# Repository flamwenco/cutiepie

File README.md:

# cutiepie
A funky little 10.5u with dual 1.75u spacebars. Support for 3u and 4u spacebar bottom row layouts has been added, as well as support for 2x2u's using the 4u top. 2u's are forced stabless, otherwise a redesign of the pcb layout would have been necessitated.

## Layout options

[An ortho pcb](https://github.com/flamwenco/cutiepie/tree/mistress/KiCad%20Project%20Files/ortho%20pcb) is also now available as well.

The vial firmware has been updated to visually support uniform stagger, regular stagger, and ortho, but your existing firmware will also work since the pinouts have not changed.

## Production files
The current version of this pcb that supports all above layouts has been ordered and confirmed to work, but I am not responsible for your orders with a pcb manu. No support will be provided, order at your own risk.

You will also need a daughterboard for this keyboard. It was designed around the ai03 C3 daughterboard.

## Case files
Case files are provided in this repo for 3d printing.

The case is designed around m2 screws and heatset inserts. The top will need 6 M2x4mm inserts, and M2x5mm screws. The daughterboard mounting in the bottom will need 4 M2x3mm inserts, and M2x4mm screws.

The cutouts for the feet in the bottom of the case are sized for primekb feet.

## Special Thanks
- [SST60](https://github.com/dededecline/SST60), this project heavily lifts the rp2040 wiring from it, without it I wouldn't have even known where to start
- 4u spacebar footprint is by [drhigsby](https://github.com/drhigsby)
- Thick plates were created from plates generated by bears' [Keyboard Case Generator](https://github.com/gleorepo/Keyboard-Case-Generator)
- Symmetric case and plate were modified by Chronomap
- [Baconspoon](https://github.com/baconspoon85/) for going above and beyond with new hotswap pcbs, layouts, case mods, and all sorts of other stuff.

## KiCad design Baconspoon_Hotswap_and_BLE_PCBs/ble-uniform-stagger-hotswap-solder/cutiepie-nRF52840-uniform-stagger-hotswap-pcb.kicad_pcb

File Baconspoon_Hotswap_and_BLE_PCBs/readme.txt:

Included in this directory are several PCB and plate files for Cutiepie by Flamwenco. Pay close attention to compatibility notes. Most of these PCB's and plates are NOT compatible with the original 2x1.75u and 3u case tops, or the original non-symmetrical case bottom. Choose a plate option that will support your desired layout, including stabilizers.

UPDATE: Added models for thick plates at /Baconspoon_Hotswap_and_BLE_PCBs/thick-plate-models. There are separate models for standard row stagger, uniform row stagger, and ortho. All three plates are for the 2x2u or 4u spacebar layout only. Stagger plates support the ISO P-key.

UPDATE: Added model for ortho PCB top case at /Case Files/Symmetrical 4u 2x2u Case/Orthopie Top Case - Baconspoon
This model is only compatible with the symmetrical case (2x2u or 4u spacebar) and add a central half unit blocker where the two alpha sections split.
	
-Hotswap, Uniform Stagger PCB
	-Integrated RP2040
	-No ISO Enter support
	-Uses uniform 0.25u stagger, as with the original cutiepie
	-Support for both 2u x 2 and 4u stabilizers.
	-Requires the symmetrical uniform or dual stagger plate for 2u stabilizer support.
	-Requires the symmetrical top and bottom cases with only 2x2u or 4u spacebar support.
	-Compatible with original "cutiepie2040" PCB firmware due to 1-for-1 pinout match.

-Hotswap, Standard Stagger PCB
	-Integrated RP2040
	-No ISO Enter support
	-Option for uniform 0.25u stagger, or traditional 0.5u stagger between the "A" and "Z" row.
	-Support for both 2u x 2 and 4u stabilizers.
	-Requires the symmetrical standard or dual stagger plate for 2u stabilizer support.
	-Requires the symmetrical top and bottom cases with only 2x2u or 4u spacebar support.
	-Compatible with original "cutiepie2040" PCB firmware due to 1-for-1 pinout match.

-Hotswap, Dual Stagger PCB
	-Made to replace uniform and standard stagger hotswap PCBs by supporting both layouts
	-Restores ISO P key support. To access stab support for ISO P, it is necessary to remove the hotswap socket for 1.5u P. Alternatively, a custom plate can be cut to support  a plate mount stabilizer. DXF and Gerber files for that plate will be made available in the repo.
	-Other features and case requirements are identical to the PCBs being replaced.

-Hotswap and Solder, Ortho PCB
	-Integrated RP2040
	-Supports 2x2u, 4u, and 2x1.75u spacebar layouts from original Flamwenco orthopie design.
	-2x1.75u spacebar layout is solder only and requires the removal of a breakaway tab to fit the appropriate case.
	-3u spacebar layout is not supported.
	-All supported layouts can be soldered. Soldered switches will be north-facing. Hotswap sockets are south-facing.
	-Compatible with vial firmware release for "orthopie" PCB due to 1-for-1 pinout match.

-Solder Only, Dual Stagger (Uniform and Standard) BLE PCB
	-Still in development
	-Integrated nRF52840 via Holyiot-18010-nRF52840 module
	-No ISO Enter support
	-Option for traditional 0.5u stagger between the "A" and "Z" row.
	-Support for both 2u x 2 and 4u stabilizers.
	-Requires the symmetrical standard or dual stagger plate for 2u stabilizer support.
	-Requires the symmetrical top and bottom cases with only 2x2u or 4u spacebar support.
	-Custom ZMK firmware

-Dual Stagger Plate
	-Maintains ISO switch and stabilizers support.
	-"Z" row switch cutouts support both standard and uniform stagger.
	-May be difficult to achieve perfect left-to-right alignment with 3-pin switches. 5-pin is recommended.
	-Gerbers for FR4 plates included with KiCad project files.

-Standard Stagger and Uniform Stagger Plates (separate)
	-Maintains ISO switch and stabilizers support for future compatibility with symmetrical case PCBs supporting ISO Enter.
	-Separate plates for each stagger option for better alignment with 3-pin switches.
	-Gerbers for FR4 plates included with KiCad project files.

-Ortho Plus Dual Stagger Universal Plate
	-Supports both ortho and stagger layout options.
	-Supports only 2x2u and 4u spacebar layouts.
	-Supports ISO P key with stabilizers.
	-Requires summetrical case design for 2x2u and 4u spacebar layouts.
	-Ortho build requires case with central 1.5u blocker to cover holes for staggered layouts.

-Ortho Plate
	-Supports ortho only, either 4u, 2x2u, or 2x1.75u spacebar layouts.
	-Works with or without central 1.5u blocker in the case.

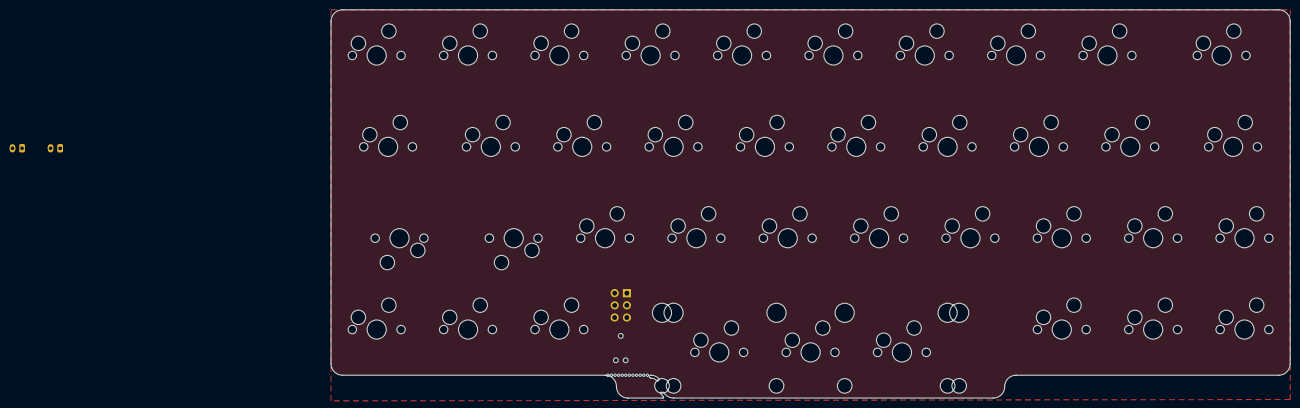
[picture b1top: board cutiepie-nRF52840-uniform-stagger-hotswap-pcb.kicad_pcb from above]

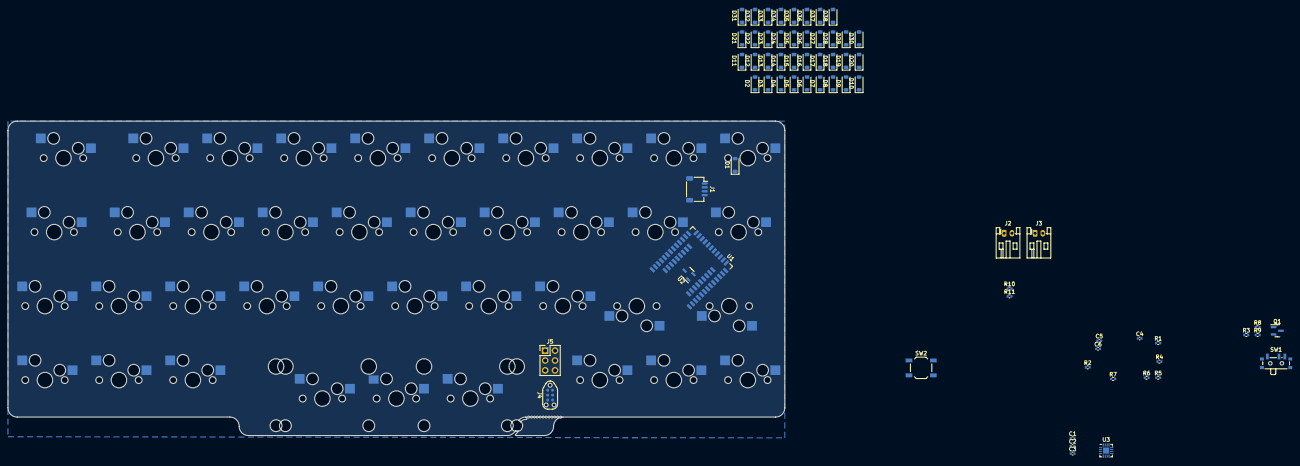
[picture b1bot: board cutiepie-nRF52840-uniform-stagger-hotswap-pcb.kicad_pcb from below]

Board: 2 copper layers, 200.0 x 81.0 mm, 106 parts (67 on the bottom side), 73 nets, no tracks yet.

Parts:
C1, C2: 1uF; C_0402_1005Metric
C3: 100nF; C_0402_1005Metric
C4, C5, C6: 4u7; C_0402_1005Metric
D1, D2, D3, D4, D5, D6, D7, D8, D9, D10, D11, D12, D13, D14, D15, D16, D17, D18, D19, D20, D21, D22, D23, D24, D25, D26, D27, D28, D29, D30, D31, D32, D33, D34, D35, D36, D37, D38: 1N4148W; D_SOD-123
H1: Cutiepie Tab; cutiepie-tab
J1: SM04B; JST_SH_SM04B-SRSS-TB_1x04-1MP_P1.00mm_Horizontal
J2, J3: Battery; JST_PH_S2B-PH-K_1x02_P2.00mm_Horizontal
J4: TC2030_SWD; CON_TC2030_outlined
J5: Conn_02x03_Counter_Clockwise; PinHeader_2x03_P2.54mm_Vertical
MX1, MX2, MX3, MX4, MX5, MX6, MX7, MX8, MX9, MX12, MX13, MX14, MX15, MX16, MX17, MX18, MX19, MX22, MX23, MX24, MX25, MX26, MX27, MX28, MX29, MX30, MX31, MX32, MX33, MX37, MX38, MX39: CPG151101S11; MXOnly-1U-Hotswap
MX10, MX21: CPG151101S11; MXOnly-1.5U-Hotswap
MX11, MX20: CPG151101S11; MXOnly-1.25U-Hotswap
MX34, MX35, MX36: CPG151101S11; MXOnly-2U-Hotswap-ReversedStabilizers
Q1: 2N7002; SOT-23
R1: 47k; R_0402_1005Metric
R2, R9: 10k; R_0402_1005Metric
R3: 100k; R_0402_1005Metric
R4, R5, R6, R7: 1k5; R_0402_1005Metric
R8: 100; R_0402_1005Metric
R10: 806kΩ; R_0402_1005Metric
R11: 2MΩ; R_0402_1005Metric
SW1: SW_SPDT; SW_SPDT_PCM12
SW2: RESET; SW_SPST_TL3342
U1: nRF52840_holyiot_18010
U2: XC6206P332MR; SOT-23-3
U3: BQ24075RGT; VQFN-16-1EP_3x3mm_P0.5mm_EP1.6x1.6mm

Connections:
+3V3: C2.2, C3.2, J4.1 (VCC), J5.1, U1.14 (VDD_nRF), U2.2 (VO)
+5V: C4.1, J1.1, R8.1, U1.22 (VBUS), U3.13 (IN)
+BATT: C6.1, J2.1, J3.1, R3.1, U3.2 (BAT), U3.3 (BAT)
+VSW: C1.2, C5.1, R7.2, R10.1, U2.3 (VI), U3.6 (EN1), U3.10 (OUT), U3.11 (OUT)
GND: C1.1, C2.1, C3.1, C4.2, C5.2, C6.2, J1.4, J2.2, J3.2, J4.5 (GND), J5.5, Q1.2 (S), R1.1, R2.2, R4.1, R5.1, R9.2, R11.2, SW1.3 (C), SW2.2, U1.1 (GND), U1.25 (GND), U1.37 (GND), U2.1 (GND), U3.4 (~CE), U3.5 (EN2), U3.8 (VSS), U3.17 (VSS)
unnamed: D1.2 (A), MX1.2 (ROW)
unnamed: D2.2 (A), MX2.2 (ROW)
unnamed: D3.2 (A), MX3.2 (ROW)
unnamed: D4.2 (A), MX4.2 (ROW)
unnamed: D5.2 (A), MX5.2 (ROW)
unnamed: D6.2 (A), MX6.2 (ROW)
unnamed: D7.2 (A), MX7.2 (ROW)
unnamed: D8.2 (A), MX8.2 (ROW)
unnamed: D9.2 (A), MX9.2 (ROW)
unnamed: D10.2 (A), MX10.2 (ROW)
unnamed: D11.2 (A), MX11.2 (ROW)
unnamed: D12.2 (A), MX12.2 (ROW)
unnamed: D13.2 (A), MX13.2 (ROW)
unnamed: D14.2 (A), MX14.2 (ROW)
unnamed: D15.2 (A), MX15.2 (ROW)
unnamed: D16.2 (A), MX16.2 (ROW)
unnamed: D17.2 (A), MX17.2 (ROW)
unnamed: D18.2 (A), MX18.2 (ROW)
unnamed: D19.2 (A), MX19.2 (ROW)
unnamed: D20.2 (A), MX20.2 (ROW)
unnamed: D21.2 (A), MX21.2 (ROW)
unnamed: D22.2 (A), MX22.2 (ROW)
unnamed: D23.2 (A), MX23.2 (ROW)
unnamed: D24.2 (A), MX24.2 (ROW)
unnamed: D25.2 (A), MX25.2 (ROW)
unnamed: D26.2 (A), MX26.2 (ROW)
unnamed: D27.2 (A), MX27.2 (ROW)
unnamed: D28.2 (A), MX28.2 (ROW)
unnamed: D29.2 (A), MX29.2 (ROW)
unnamed: D30.2 (A), MX30.2 (ROW)
unnamed: D31.2 (A), MX31.2 (ROW)
unnamed: D32.2 (A), MX32.2 (ROW)
unnamed: D33.2 (A), MX33.2 (ROW)
unnamed: D34.2 (A), MX34.2 (ROW), MX35.2 (ROW)
unnamed: D35.2 (A), MX36.2 (ROW)
unnamed: D36.2 (A), MX37.2 (ROW)
unnamed: D37.2 (A), MX38.2 (ROW)
unnamed: D38.2 (A), MX39.2 (ROW)
unnamed: Q1.1 (G), R8.2, R9.1
unnamed: R5.2, R6.1
unnamed: R3.2, SW1.1 (A)
unnamed: R4.2, U3.12 (ILIM)
unnamed: R6.2, U3.16 (ISET)
unnamed: R1.2, U3.14 (TMR)
unnamed: R2.1, U3.1 (TS)
unnamed: R7.1, U3.9 (~CHG)
RESET: J4.3 (~RST), J5.3, SW2.1, U1.21 (P0.18-RESET)
SWDCLK: J4.4 (SWCLK), J5.4, U1.31 (SWDCLK)
SWDIO: J4.2 (SWDIO), J5.2, U1.32 (SWDIO)
SWO: J4.6 (SWO), J5.6
SYSOFF: Q1.3 (D), SW1.2 (B), U3.15 (SYSOFF)
USB_D+: J1.3, U1.24 (D+)
USB_D-: J1.2, U1.23 (D-)
VSENSE: R10.2, R11.1, U1.11 (P0.31-LF-A)
col0: MX1.1 (COL), MX11.1 (COL), MX21.1 (COL), MX31.1 (COL)
col1: MX2.1 (COL), MX12.1 (COL), MX22.1 (COL), MX32.1 (COL)
col2: MX3.1 (COL), MX13.1 (COL), MX23.1 (COL), MX33.1 (COL)
col3: MX4.1 (COL), MX14.1 (COL), MX24.1 (COL)
col4: MX5.1 (COL), MX15.1 (COL), MX25.1 (COL), MX34.1 (COL), MX35.1 (COL)
col5: MX6.1 (COL), MX16.1 (COL), MX26.1 (COL), MX36.1 (COL)
col6: MX7.1 (COL), MX17.1 (COL), MX27.1 (COL)
col7: MX8.1 (COL), MX18.1 (COL), MX28.1 (COL), MX37.1 (COL)
col8: MX9.1 (COL), MX19.1 (COL), MX29.1 (COL), MX38.1 (COL)
col9: MX10.1 (COL), MX20.1 (COL), MX30.1 (COL), MX39.1 (COL)
row0: D1.1 (K), D2.1 (K), D3.1 (K), D4.1 (K), D5.1 (K), D6.1 (K), D7.1 (K), D8.1 (K), D9.1 (K), D10.1 (K)
row1: D11.1 (K), D12.1 (K), D13.1 (K), D14.1 (K), D15.1 (K), D16.1 (K), D17.1 (K), D18.1 (K), D19.1 (K), D20.1 (K)
row2: D21.1 (K), D22.1 (K), D23.1 (K), D24.1 (K), D25.1 (K), D26.1 (K), D27.1 (K), D28.1 (K), D29.1 (K), D30.1 (K)
row3: D31.1 (K), D32.1 (K), D33.1 (K), D34.1 (K), D35.1 (K), D36.1 (K), D37.1 (K), D38.1 (K)

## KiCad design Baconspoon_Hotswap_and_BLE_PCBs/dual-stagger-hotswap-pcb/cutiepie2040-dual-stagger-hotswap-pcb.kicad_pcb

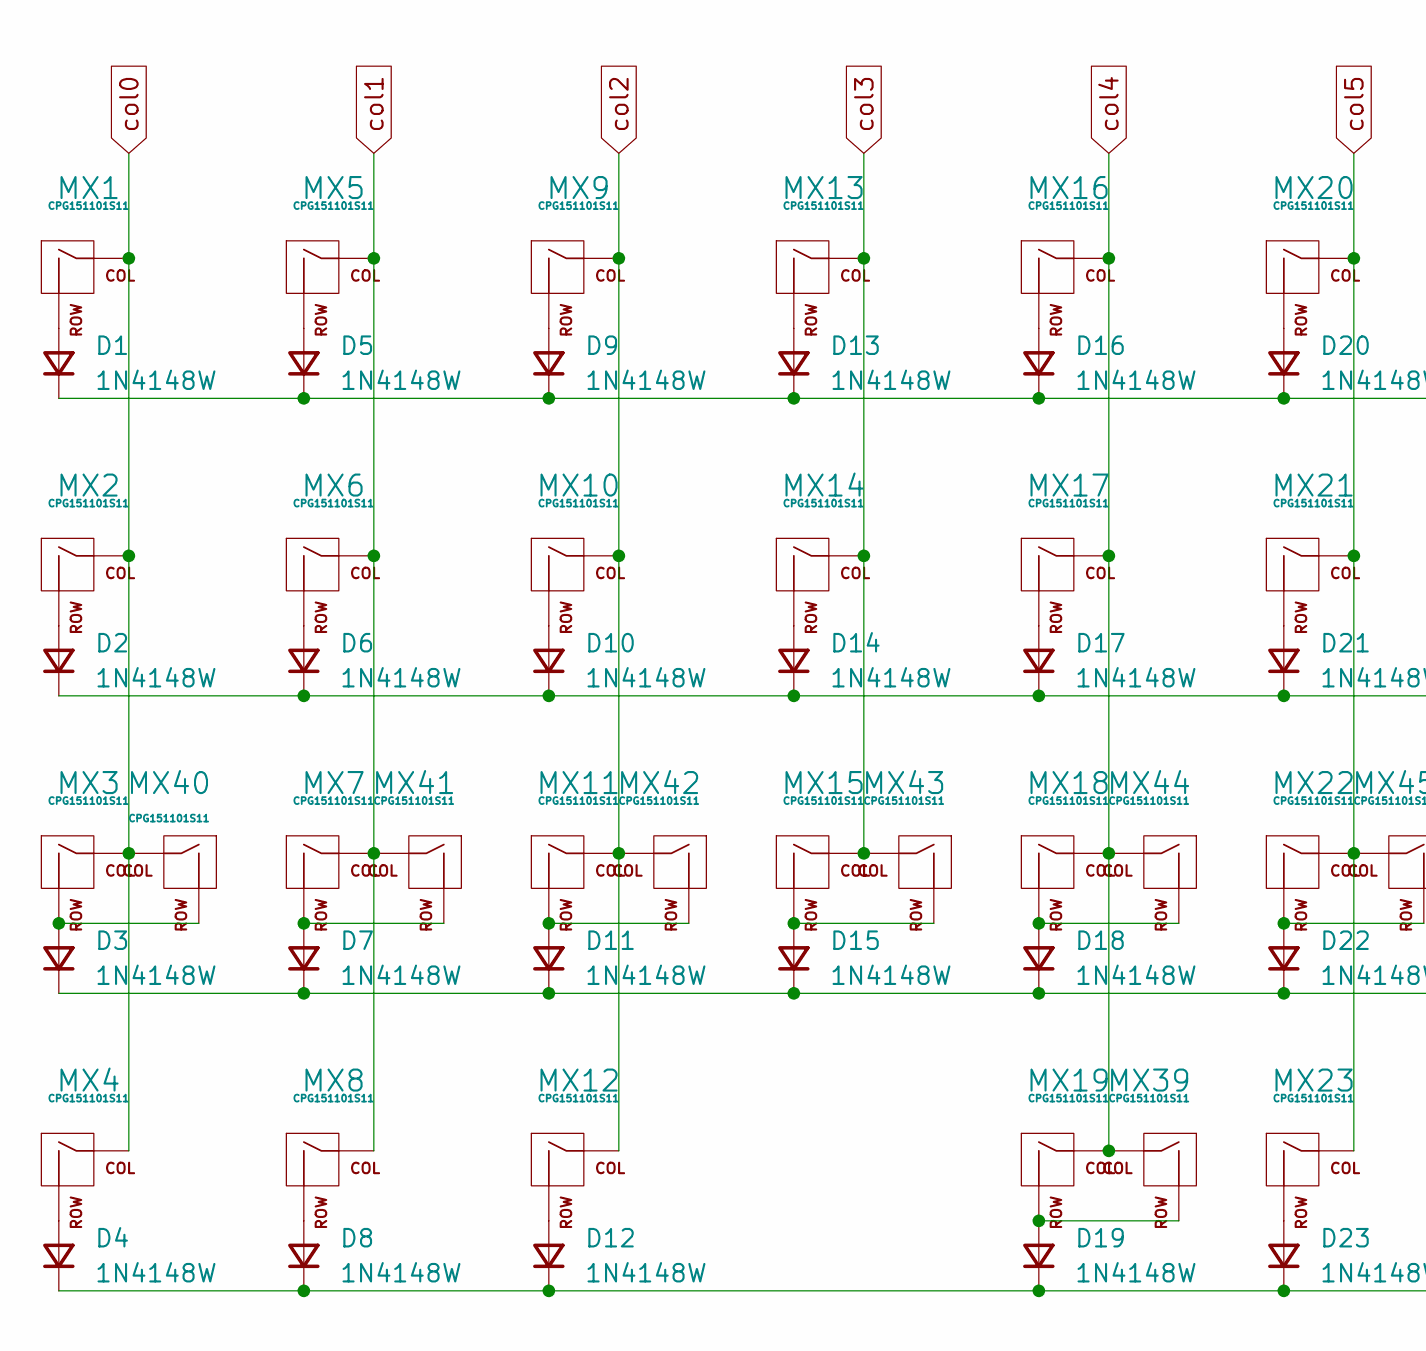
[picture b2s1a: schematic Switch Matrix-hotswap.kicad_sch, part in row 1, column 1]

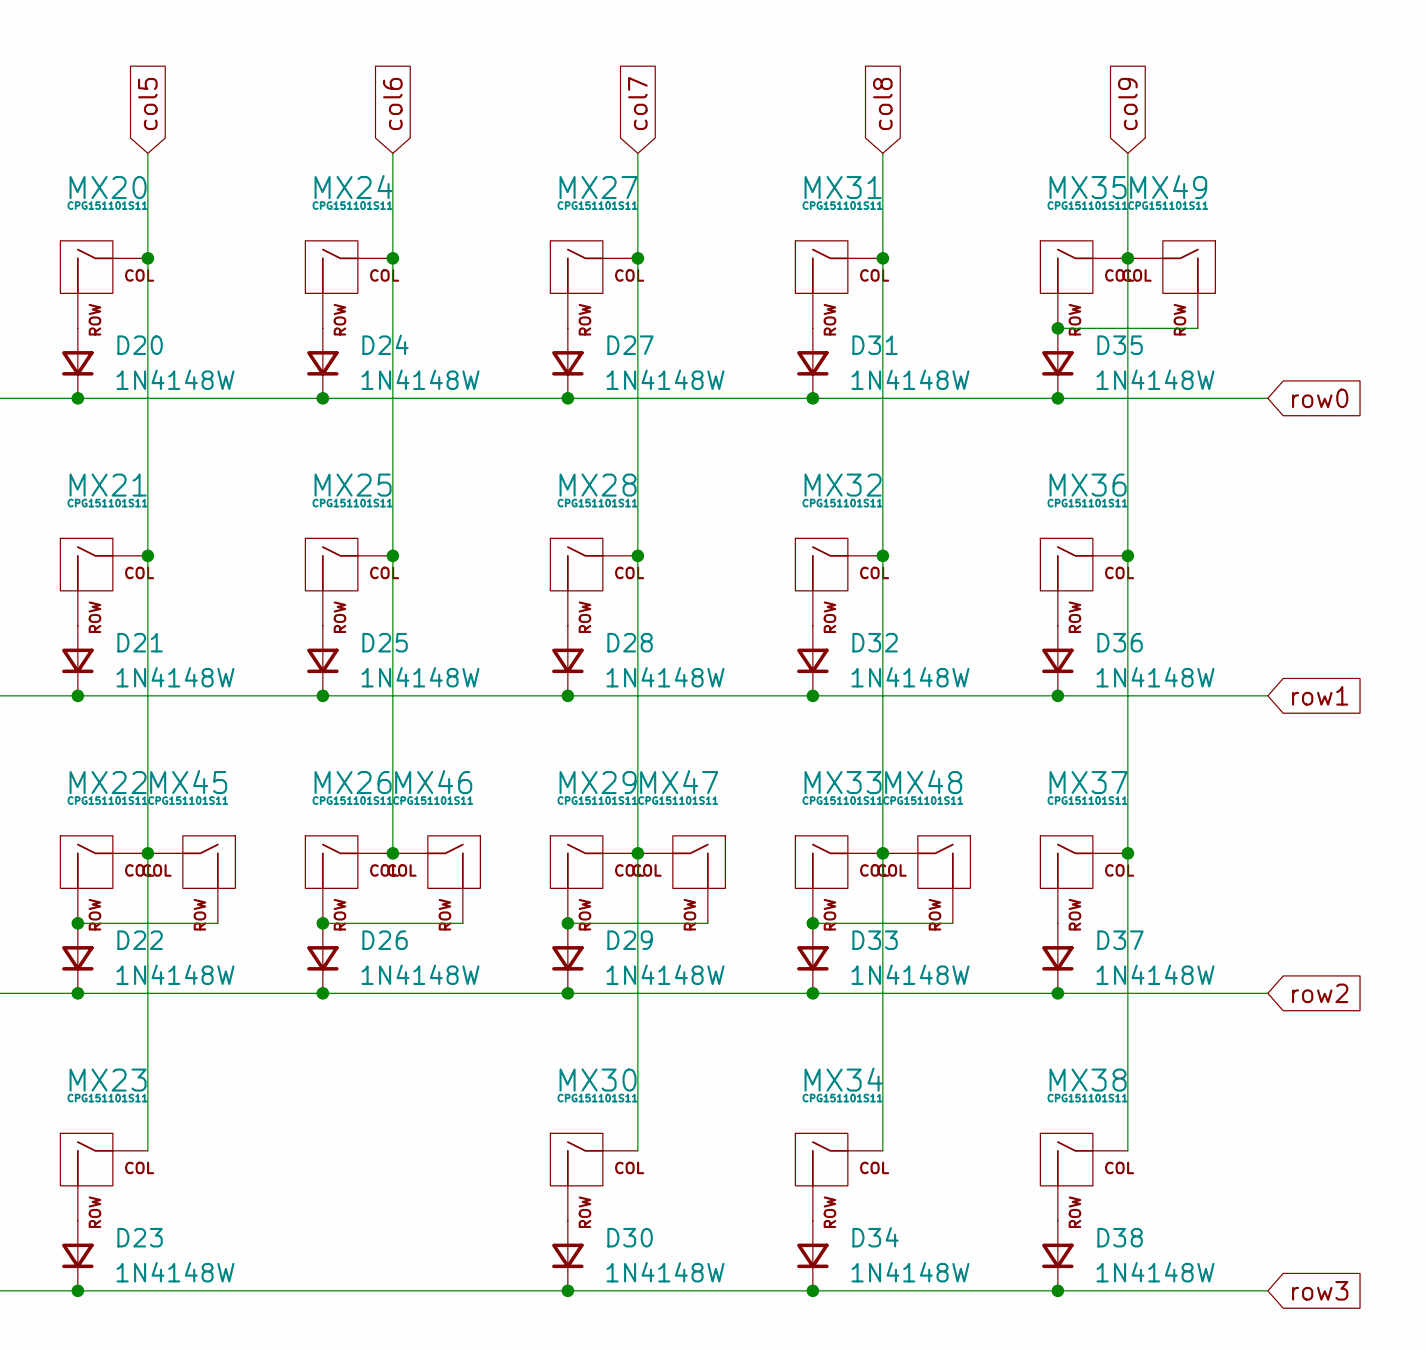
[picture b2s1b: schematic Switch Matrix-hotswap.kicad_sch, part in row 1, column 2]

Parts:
D1, D2, D3, D4, D5, D6, D7, D8, D9, D10, D11, D12, D13, D14, D15, D16, D17, D18, D19, D20, D21, D22, D23, D24, D25, D26, D27, D28, D29, D30, D31, D32, D33, D34, D35, D36, D37, D38: 1N4148W; D_SOD-123
MX1, MX4, MX5, MX6, MX7, MX8, MX9, MX10, MX11, MX12, MX13, MX14, MX15, MX16, MX17, MX18, MX20, MX21, MX22, MX24, MX25, MX26, MX27, MX28, MX29, MX30, MX31, MX32, MX33, MX34, MX37, MX38, MX41, MX42, MX43, MX44, MX45, MX46, MX47: CPG151101S11; MXOnly-1U-Hotswap; LCSC C2803348
MX2, MX36: CPG151101S11; MXOnly-1.25U-Hotswap; LCSC C2803348
MX3, MX35: CPG151101S11; MXOnly-1.5U-Hotswap; LCSC C2803348
MX19, MX23, MX39: CPG151101S11; MXOnly-2U-Hotswap-ReversedStabilizers; LCSC C2803348
MX40, MX48: CPG151101S11; MXOnly-1.75U-Hotswap; LCSC C2803348
MX49: CPG151101S11; MXOnly-ISO-Hotswap-ReversedStabilizers; LCSC C2803348

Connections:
unnamed: D1.2 (A), MX1.2 (ROW)
unnamed: D2.2 (A), MX2.2 (ROW)
unnamed: D3.2 (A), MX3.2 (ROW), MX40.2 (ROW)
unnamed: D4.2 (A), MX4.2 (ROW)
unnamed: D5.2 (A), MX5.2 (ROW)
unnamed: D6.2 (A), MX6.2 (ROW)
unnamed: D7.2 (A), MX7.2 (ROW), MX41.2 (ROW)
unnamed: D8.2 (A), MX8.2 (ROW)
unnamed: D9.2 (A), MX9.2 (ROW)
unnamed: D10.2 (A), MX10.2 (ROW)
unnamed: D11.2 (A), MX11.2 (ROW), MX42.2 (ROW)
unnamed: D12.2 (A), MX12.2 (ROW)
unnamed: D13.2 (A), MX13.2 (ROW)
unnamed: D14.2 (A), MX14.2 (ROW)
unnamed: D15.2 (A), MX15.2 (ROW), MX43.2 (ROW)
unnamed: D16.2 (A), MX16.2 (ROW)
unnamed: D17.2 (A), MX17.2 (ROW)
unnamed: D18.2 (A), MX18.2 (ROW), MX44.2 (ROW)
unnamed: D19.2 (A), MX19.2 (ROW), MX39.2 (ROW)
unnamed: D20.2 (A), MX20.2 (ROW)
unnamed: D21.2 (A), MX21.2 (ROW)
unnamed: D22.2 (A), MX22.2 (ROW), MX45.2 (ROW)
unnamed: D23.2 (A), MX23.2 (ROW)
unnamed: D24.2 (A), MX24.2 (ROW)
unnamed: D25.2 (A), MX25.2 (ROW)
unnamed: D26.2 (A), MX26.2 (ROW), MX46.2 (ROW)
unnamed: D27.2 (A), MX27.2 (ROW)
unnamed: D28.2 (A), MX28.2 (ROW)
unnamed: D29.2 (A), MX29.2 (ROW), MX47.2 (ROW)
unnamed: D30.2 (A), MX30.2 (ROW)
unnamed: D31.2 (A), MX31.2 (ROW)
unnamed: D32.2 (A), MX32.2 (ROW)
unnamed: D33.2 (A), MX33.2 (ROW), MX48.2 (ROW)
unnamed: D34.2 (A), MX34.2 (ROW)
unnamed: D35.2 (A), MX35.2 (ROW), MX49.2 (ROW)
unnamed: D36.2 (A), MX36.2 (ROW)
unnamed: D37.2 (A), MX37.2 (ROW)
unnamed: D38.2 (A), MX38.2 (ROW)
col0: MX1.1 (COL), MX2.1 (COL), MX3.1 (COL), MX4.1 (COL), MX40.1 (COL); also elsewhere on the board
col1: MX5.1 (COL), MX6.1 (COL), MX7.1 (COL), MX8.1 (COL), MX41.1 (COL); also elsewhere on the board
col2: MX9.1 (COL), MX10.1 (COL), MX11.1 (COL), MX12.1 (COL), MX42.1 (COL); also elsewhere on the board
col3: MX13.1 (COL), MX14.1 (COL), MX15.1 (COL), MX43.1 (COL); also elsewhere on the board
col4: MX16.1 (COL), MX17.1 (COL), MX18.1 (COL), MX19.1 (COL), MX39.1 (COL), MX44.1 (COL); also elsewhere on the board
col5: MX20.1 (COL), MX21.1 (COL), MX22.1 (COL), MX23.1 (COL), MX45.1 (COL); also elsewhere on the board
col6: MX24.1 (COL), MX25.1 (COL), MX26.1 (COL), MX46.1 (COL); also elsewhere on the board
col7: MX27.1 (COL), MX28.1 (COL), MX29.1 (COL), MX30.1 (COL), MX47.1 (COL); also elsewhere on the board
col8: MX31.1 (COL), MX32.1 (COL), MX33.1 (COL), MX34.1 (COL), MX48.1 (COL); also elsewhere on the board
col9: MX35.1 (COL), MX36.1 (COL), MX37.1 (COL), MX38.1 (COL), MX49.1 (COL); also elsewhere on the board
row0: D1.1 (K), D5.1 (K), D9.1 (K), D13.1 (K), D16.1 (K), D20.1 (K), D24.1 (K), D27.1 (K), D31.1 (K), D35.1 (K); also elsewhere on the board
row1: D2.1 (K), D6.1 (K), D10.1 (K), D14.1 (K), D17.1 (K), D21.1 (K), D25.1 (K), D28.1 (K), D32.1 (K), D36.1 (K); also elsewhere on the board
row2: D3.1 (K), D7.1 (K), D11.1 (K), D15.1 (K), D18.1 (K), D22.1 (K), D26.1 (K), D29.1 (K), D33.1 (K), D37.1 (K); also elsewhere on the board
row3: D4.1 (K), D8.1 (K), D12.1 (K), D19.1 (K), D23.1 (K), D30.1 (K), D34.1 (K), D38.1 (K); also elsewhere on the board

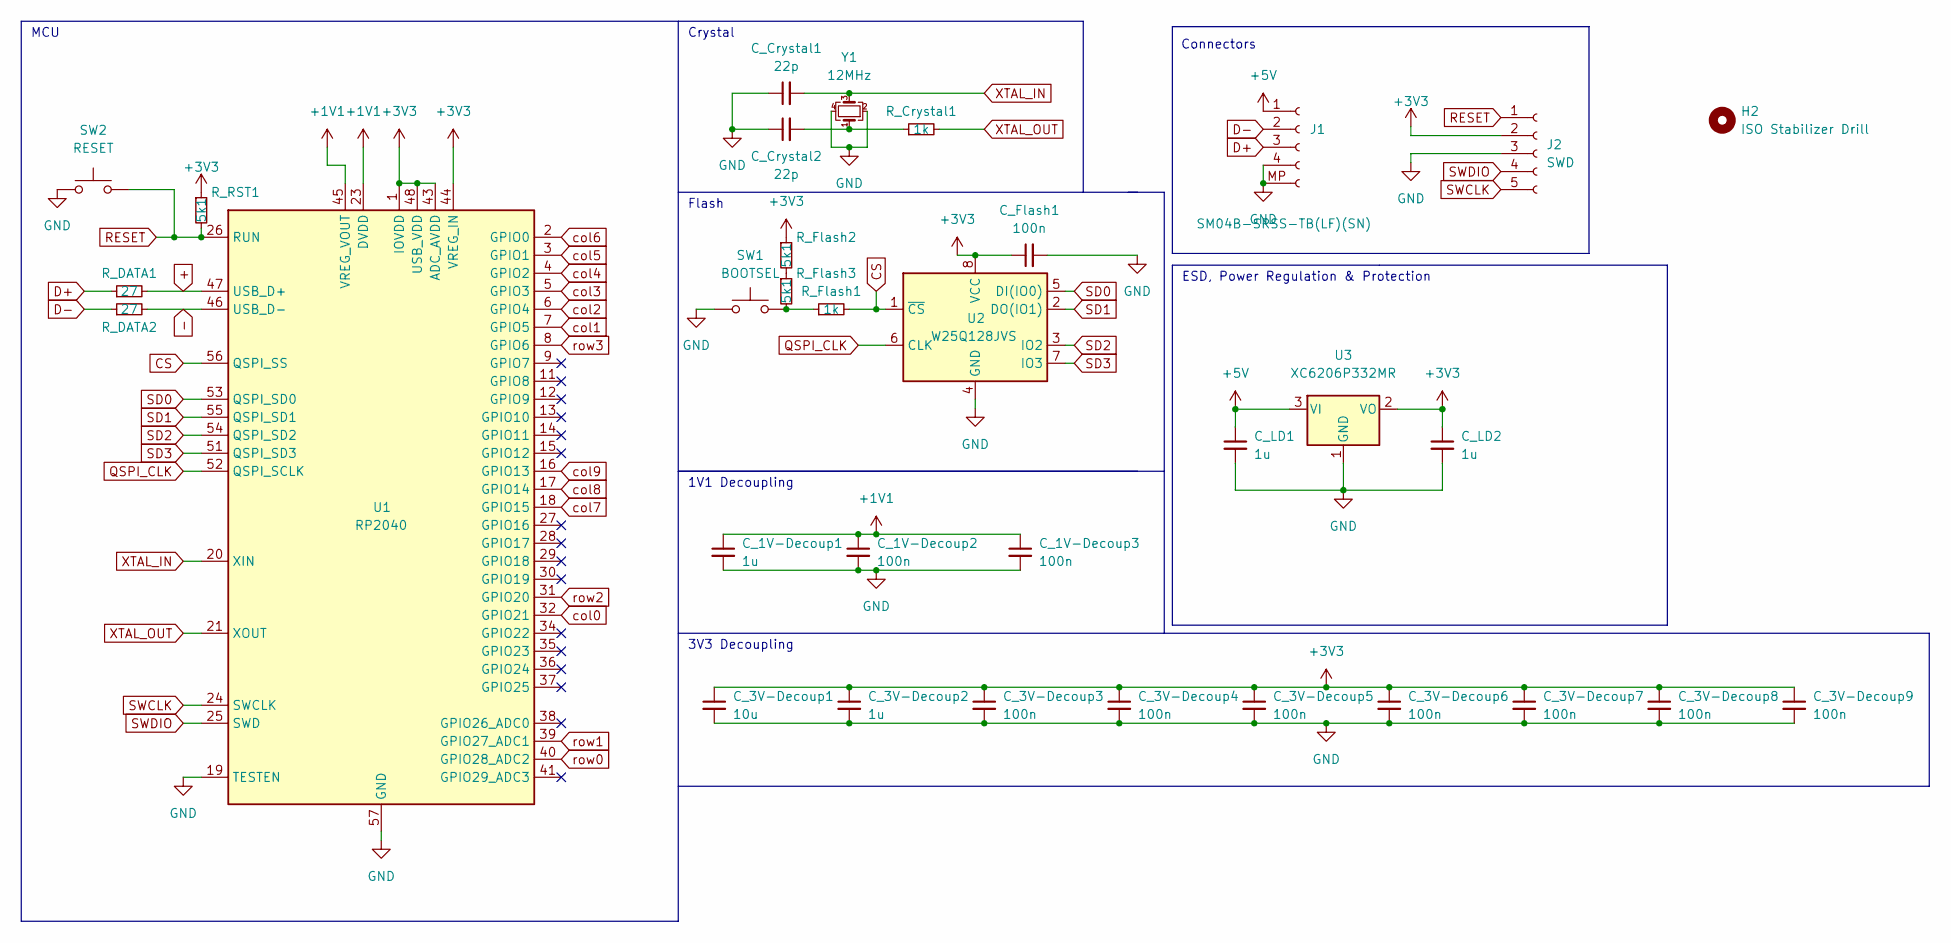
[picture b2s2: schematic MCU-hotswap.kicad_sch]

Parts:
C_1V-Decoup1, C_3V-Decoup2: 1u; C_0402_1005Metric
C_1V-Decoup2, C_1V-Decoup3, C_3V-Decoup3, C_3V-Decoup4, C_3V-Decoup5, C_3V-Decoup6, C_3V-Decoup7, C_3V-Decoup8, C_3V-Decoup9: 100n; C_0402_1005Metric
C_3V-Decoup1: 10u; C_0402_1005Metric
C_Crystal1, C_Crystal2: 22p; C_0402_1005Metric
C_Flash1: 100n; C_0402_1005Metric
C_LD1, C_LD2: 1u; C_0402_1005Metric
H2: ISO Stabilizer Drill; MXOnly-ISO-NoSwitch
J1: SM04B-SRSS-TB(LF)(SN); JST_SH_SM04B-SRSS-TB_1x04-1MP_P1.00mm_Horizontal; LCSC C160404
J2: SWD; PinHeader_1x05_P2.54mm_Vertical
R_Crystal1: 1k; R_0402_1005Metric
R_DATA1, R_DATA2: 27; R_0402_1005Metric
R_Flash1: 1k; R_0402_1005Metric
R_Flash2, R_Flash3: 5k1; R_0402_1005Metric
R_RST1: 5k1; R_0402_1005Metric
SW1: BOOTSEL; SW_SPST_TL3342; LCSC C318884
SW2: RESET; SW_SPST_TL3342; LCSC C318884
U1: RP2040; RP2040-QFN-56; LCSC C2040
U2: W25Q128JVS; SOIC-8_5.23x5.23mm_P1.27mm; LCSC C2613930
U3: XC6206P332MR; SOT-23; LCSC C5446
Y1: 12MHz; Crystal_SMD_3225-4Pin_3.2x2.5mm; LCSC C9002

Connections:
+: R_DATA1.2, U1.47 (USB_D+)
+1V1: C_1V-Decoup1.1, C_1V-Decoup2.1, C_1V-Decoup3.1, U1.23 (DVDD), U1.45 (VREG_VOUT), U1.50 (DVDD)
+3V3: C_3V-Decoup1.1, C_3V-Decoup2.1, C_3V-Decoup3.1, C_3V-Decoup4.1, C_3V-Decoup5.1, C_3V-Decoup6.1, C_3V-Decoup7.1, C_3V-Decoup8.1, C_3V-Decoup9.1, C_Flash1.1, C_LD2.1, J2.2, R_Flash2.1, R_RST1.1, U1.1 (IOVDD), U1.10 (IOVDD), U1.22 (IOVDD), U1.33 (IOVDD), U1.42 (IOVDD), U1.43 (ADC_AVDD), U1.44 (VREG_IN), U1.48 (USB_VDD), U1.49 (IOVDD), U2.8 (VCC), U3.2 (VO)
+5V: C_LD1.1, J1.1, U3.3 (VI)
-: R_DATA2.2, U1.46 (USB_D-)
CS: R_Flash1.2, U1.56 (QSPI_SS), U2.1 (~CS)
D+: J1.3, R_DATA1.1
D-: J1.2, R_DATA2.1
GND: C_1V-Decoup1.2, C_1V-Decoup2.2, C_1V-Decoup3.2, C_3V-Decoup1.2, C_3V-Decoup2.2, C_3V-Decoup3.2, C_3V-Decoup4.2, C_3V-Decoup5.2, C_3V-Decoup6.2, C_3V-Decoup7.2, C_3V-Decoup8.2, C_3V-Decoup9.2, C_Crystal1.1, C_Crystal2.1, C_Flash1.2, C_LD1.2, C_LD2.2, J1.4, J1.MP, J2.3, SW1.1, SW2.1, U1.19 (TESTEN), U1.57 (GND), U2.4 (GND), U3.1 (GND), Y1.2, Y1.4
unnamed: C_Crystal2.2, R_Crystal1.1, Y1.1
unnamed: R_Flash1.1, R_Flash3.2, SW1.2
unnamed: R_Flash2.2, R_Flash3.1
QSPI_CLK: U1.52 (QSPI_SCLK), U2.6 (CLK)
RESET: J2.1, R_RST1.2, SW2.2, U1.26 (RUN)
SD0: U1.53 (QSPI_SD0), U2.5 (DI(IO0))
SD1: U1.55 (QSPI_SD1), U2.2 (DO(IO1))
SD2: U1.54 (QSPI_SD2), U2.3 (IO2)
SD3: U1.51 (QSPI_SD3), U2.7 (IO3)
SWCLK: J2.5, U1.24 (SWCLK)
SWDIO: J2.4, U1.25 (SWD)
XTAL_IN: C_Crystal1.2, U1.20 (XIN), Y1.3
XTAL_OUT: R_Crystal1.2, U1.21 (XOUT)
col0: U1.32 (GPIO21); also elsewhere on the board
col1: U1.7 (GPIO5); also elsewhere on the board
col2: U1.6 (GPIO4); also elsewhere on the board
col3: U1.5 (GPIO3); also elsewhere on the board
col4: U1.4 (GPIO2); also elsewhere on the board
col5: U1.3 (GPIO1); also elsewhere on the board
col6: U1.2 (GPIO0); also elsewhere on the board
col7: U1.18 (GPIO15); also elsewhere on the board
col8: U1.17 (GPIO14); also elsewhere on the board
col9: U1.16 (GPIO13); also elsewhere on the board
row0: U1.40 (GPIO28_ADC2); also elsewhere on the board
row1: U1.39 (GPIO27_ADC1); also elsewhere on the board
row2: U1.31 (GPIO20); also elsewhere on the board
row3: U1.8 (GPIO6); also elsewhere on the board

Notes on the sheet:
Connectors
1V1 Decoupling
ESD, Power Regulation & Protection
Crystal
MCU
Flash
3V3 Decoupling

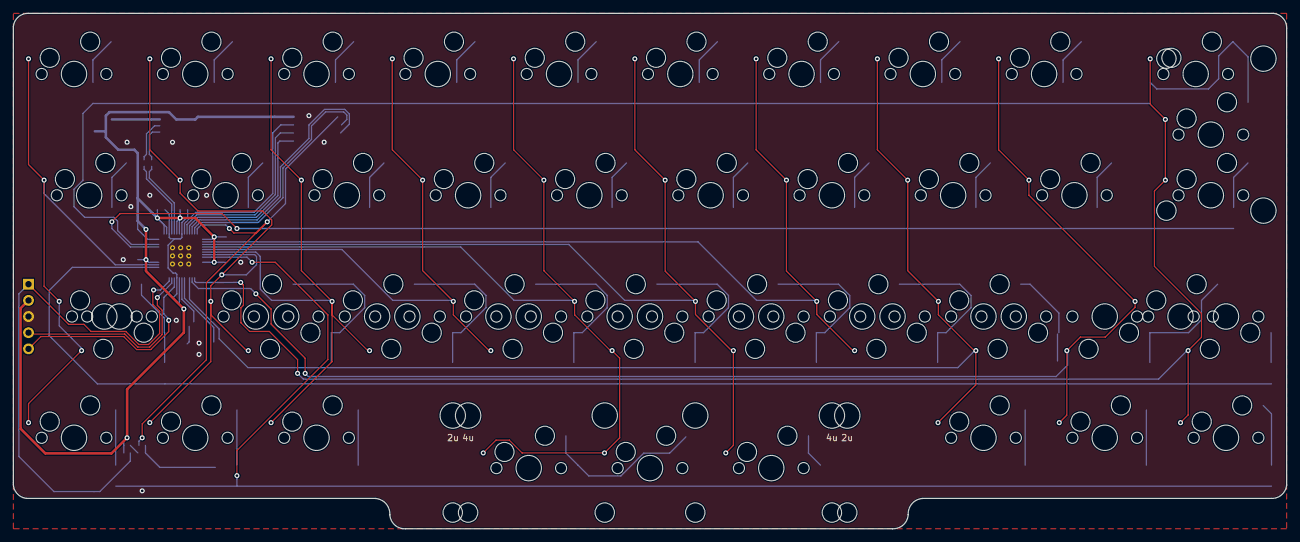
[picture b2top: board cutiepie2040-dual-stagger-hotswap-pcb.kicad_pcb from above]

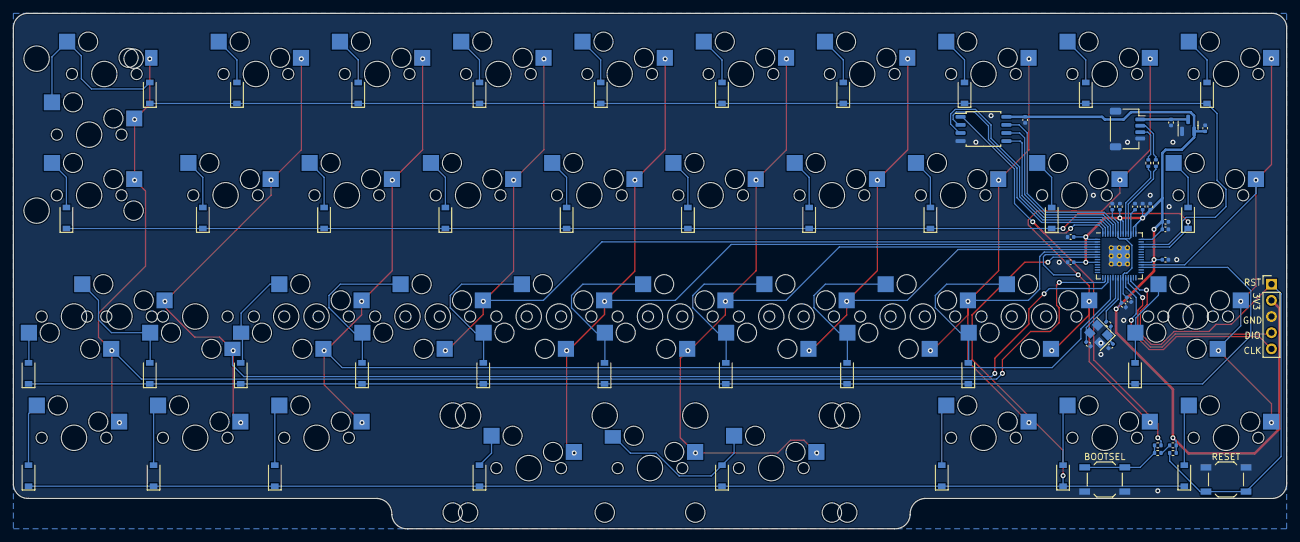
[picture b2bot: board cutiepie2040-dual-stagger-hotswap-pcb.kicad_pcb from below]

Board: 2 copper layers, 200.0 x 81.0 mm, 120 parts (119 on the bottom side), 74 nets.

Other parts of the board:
H1: ISO Stabilizer Drill; MXOnly-ISO-NoSwitch

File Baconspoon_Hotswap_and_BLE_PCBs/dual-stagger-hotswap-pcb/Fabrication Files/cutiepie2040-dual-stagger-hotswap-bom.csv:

Comment,Designator,Footprint,JLCPCB Part#(optional)
1uF,C_1V-Decoup1,C_0402_1005Metric,C52923
100nF,C_1V-Decoup2,C_0402_1005Metric,C2991468
100nF,C_1V-Decoup3,C_0402_1005Metric,C2991468
10uF,C_3V-Decoup1,C_0402_1005Metric,C15525
1uF,C_3V-Decoup2,C_0402_1005Metric,C52923
100nF,C_3V-Decoup3,C_0402_1005Metric,C2991468
100nF,C_3V-Decoup4,C_0402_1005Metric,C2991468
100nF,C_3V-Decoup5,C_0402_1005Metric,C2991468
100nF,C_3V-Decoup6,C_0402_1005Metric,C2991468
100nF,C_3V-Decoup7,C_0402_1005Metric,C2991468
100nF,C_3V-Decoup8,C_0402_1005Metric,C2991468
100nF,C_3V-Decoup9,C_0402_1005Metric,C2991468
22pF,C_Crystal1,C_0402_1005Metric,C1555
22pF,C_Crystal2,C_0402_1005Metric,C1555
100nF,C_Flash1,C_0402_1005Metric,C2991468
1uF,C_LD1,C_0402_1005Metric,C52923
1uF,C_LD2,C_0402_1005Metric,C52923
1N4148W,D1,D_SOD-123,C81598
1N4148W,D10,D_SOD-123,C81598
1N4148W,D11,D_SOD-123,C81598
1N4148W,D12,D_SOD-123,C81598
1N4148W,D13,D_SOD-123,C81598
1N4148W,D14,D_SOD-123,C81598
1N4148W,D15,D_SOD-123,C81598
1N4148W,D16,D_SOD-123,C81598
1N4148W,D17,D_SOD-123,C81598
1N4148W,D18,D_SOD-123,C81598
1N4148W,D19,D_SOD-123,C81598
1N4148W,D2,D_SOD-123,C81598
1N4148W,D20,D_SOD-123,C81598
1N4148W,D21,D_SOD-123,C81598
1N4148W,D22,D_SOD-123,C81598
1N4148W,D23,D_SOD-123,C81598
1N4148W,D24,D_SOD-123,C81598
1N4148W,D25,D_SOD-123,C81598
1N4148W,D26,D_SOD-123,C81598
1N4148W,D27,D_SOD-123,C81598
1N4148W,D28,D_SOD-123,C81598
1N4148W,D29,D_SOD-123,C81598
1N4148W,D3,D_SOD-123,C81598
1N4148W,D30,D_SOD-123,C81598
1N4148W,D31,D_SOD-123,C81598
1N4148W,D32,D_SOD-123,C81598
1N4148W,D33,D_SOD-123,C81598
1N4148W,D34,D_SOD-123,C81598
1N4148W,D35,D_SOD-123,C81598
1N4148W,D36,D_SOD-123,C81598
1N4148W,D37,D_SOD-123,C81598
1N4148W,D38,D_SOD-123,C81598
1N4148W,D4,D_SOD-123,C81598
1N4148W,D5,D_SOD-123,C81598
1N4148W,D6,D_SOD-123,C81598
1N4148W,D7,D_SOD-123,C81598
1N4148W,D8,D_SOD-123,C81598
1N4148W,D9,D_SOD-123,C81598
SM04B-SRSS-TB(LF)(SN),J1,JST_SH_SM04B-SRSS-TB_1x04-1MP_P1.00mm_Horizontal,C160404
CPG151101S11,MX1,MXOnly-1U-Hotswap,C5156480
CPG151101S11,MX10,MXOnly-1U-Hotswap,C5156480
CPG151101S11,MX11,MXOnly-1U-Hotswap,C5156480
CPG151101S11,MX12,MXOnly-1U-Hotswap,C5156480
CPG151101S11,MX13,MXOnly-1U-Hotswap,C5156480
CPG151101S11,MX14,MXOnly-1U-Hotswap,C5156480
CPG151101S11,MX15,MXOnly-1U-Hotswap,C5156480
CPG151101S11,MX16,MXOnly-1U-Hotswap,C5156480
CPG151101S11,MX17,MXOnly-1U-Hotswap,C5156480
CPG151101S11,MX18,MXOnly-1U-Hotswap,C5156480
CPG151101S11,MX19,MXOnly-2U-Hotswap-ReversedStabilizers,C5156480
CPG151101S11,MX2,MXOnly-1.25U-Hotswap,C5156480
CPG151101S11,MX20,MXOnly-1U-Hotswap,C5156480
CPG151101S11,MX21,MXOnly-1U-Hotswap,C5156480
CPG151101S11,MX22,MXOnly-1U-Hotswap,C5156480
CPG151101S11,MX23,MXOnly-2U-Hotswap-ReversedStabilizers,C5156480
CPG151101S11,MX24,MXOnly-1U-Hotswap,C5156480
CPG151101S11,MX25,MXOnly-1U-Hotswap,C5156480
CPG151101S11,MX26,MXOnly-1U-Hotswap,C5156480
CPG151101S11,MX27,MXOnly-1U-Hotswap,C5156480
CPG151101S11,MX28,MXOnly-1U-Hotswap,C5156480
CPG151101S11,MX29,MXOnly-1U-Hotswap,C5156480
CPG151101S11,MX3,MXOnly-1.5U-Hotswap,C5156480
CPG151101S11,MX30,MXOnly-1U-Hotswap,C5156480
CPG151101S11,MX31,MXOnly-1U-Hotswap,C5156480
CPG151101S11,MX32,MXOnly-1U-Hotswap,C5156480
CPG151101S11,MX33,MXOnly-1U-Hotswap,C5156480
CPG151101S11,MX34,MXOnly-1U-Hotswap,C5156480
CPG151101S11,MX35,MXOnly-1.5U-Hotswap,C5156480
CPG151101S11,MX36,MXOnly-1.25U-Hotswap,C5156480
CPG151101S11,MX37,MXOnly-1U-Hotswap,C5156480
CPG151101S11,MX38,MXOnly-1U-Hotswap,C5156480
CPG151101S11,MX39,MXOnly-2U-Hotswap-ReversedStabilizers,C5156480
CPG151101S11,MX4,MXOnly-1U-Hotswap,C5156480
CPG151101S11,MX40,MXOnly-1.75U-Hotswap,C5156480
CPG151101S11,MX41,MXOnly-1U-Hotswap,C5156480
CPG151101S11,MX42,MXOnly-1U-Hotswap,C5156480
CPG151101S11,MX43,MXOnly-1U-Hotswap,C5156480
CPG151101S11,MX44,MXOnly-1U-Hotswap,C5156480
CPG151101S11,MX45,MXOnly-1U-Hotswap,C5156480
CPG151101S11,MX46,MXOnly-1U-Hotswap,C5156480
CPG151101S11,MX47,MXOnly-1U-Hotswap,C5156480
CPG151101S11,MX48,MXOnly-1.75U-Hotswap,C5156480
CPG151101S11,MX49,MXOnly-ISO-Hotswap-ReversedStabilizers,C5156480
CPG151101S11,MX5,MXOnly-1U-Hotswap,C5156480
CPG151101S11,MX6,MXOnly-1U-Hotswap,C5156480
CPG151101S11,MX7,MXOnly-1U-Hotswap,C5156480
CPG151101S11,MX8,MXOnly-1U-Hotswap,C5156480
CPG151101S11,MX9,MXOnly-1U-Hotswap,C5156480
1k ohm,R_Crystal1,R_0402_1005Metric,C279987
27 ohm,R_DATA1,R_0402_1005Metric,C25100
27 ohm,R_DATA2,R_0402_1005Metric,C25100
1k ohm,R_Flash1,R_0402_1005Metric,C279987
5k1 ohm,R_Flash2,R_0402_1005Metric,C103086
5k1 ohm,R_Flash3,R_0402_1005Metric,C103086
5k1 ohm,R_RST1,R_0402_1005Metric,C103086
BOOTSEL,SW1,SW_SPST_TL3342,C318884
RESET,SW2,SW_SPST_TL3342,C318884
RP2040,U1,RP2040-QFN-56,C2040
W25Q128JVS,U2,SOIC-8_5.23x5.23mm_P1.27mm,C2613930
XC6206P332MR,U3,SOT-23,C5446
12MHz,Y1,Crystal_SMD_3225-4Pin_3.2x2.5mm,C9002

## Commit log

2022-08-06 Create project and MCU schematic
2022-08-08 Complete schematic aside from switch matrix, and rename project
2022-08-08 Finish schematic, annotate footprints, start pcb creation
2022-08-08 Finish PCB and create production files
2022-08-08 Create step file of pcb
2022-08-11 Update PCB step
2022-09-07 Create rough case, update name
2022-09-08 Add ISO, 3u, and 4u support. Why do I do this to myself lol
2022-09-08 Organize case files ahead of possible future cases
2022-09-08 Add layouts image
2022-09-08 Add firmware
2022-11-08 Update files for current untested pcb, and update readme
2022-11-29 Redesign case for heat set inserts
2023-02-07 Update gerbers to fix some routing issues for the new layout
2023-02-11 pcb updates
2023-02-24 Update pcb & step
2023-02-27 Initial commit for updated case
2023-02-28 Add hail satan bottom too cuz wynaut
2023-03-02 Update readme n stuff
2023-03-29 Add 2u support to pcb
2023-03-29 More 2u changes
2023-03-29 Fix case files for 3u and 4u tops, add 2x2u thick plate
2023-07-15 Add symmetric case files, rename some files for Windows compat
2023-07-16 Added Hotswap PCB directory to KiCad Project Files with hotswap Cutiepie PCB and associated fabrication files. PCB surrently untested.
2023-07-17 initial ortho pcb commit
2023-07-17 finish routing ortho pcb, currently untested
2023-07-19 Added standard stagger hotswap PCB and moved column vias in uniform stagger hotswap PCB outside of solder pads to reduce fabrication cost.
2023-08-01 Finalized ortho pcb?
2023-08-11 Ortho pcb and firmware donezo
2023-08-12 add kicad project files for fully tested uniform stagger hotswap pcb and several plates to support standard stagger and 2u stabilizers
2023-08-12 add kicad project files for untested standard stagger hotswap pcb
2023-09-01 Update ortho plate files
2023-09-25 add 'universal' ortho plus dual-stagger plate
2023-09-25 add gerbers for 'universal' plate
2023-09-25 upload accurate fabrication files for dual-stagger hotswap PCB
2023-10-08 update readme. add hotwap + solder orthopie pcb, howswap dual stagger pcb, and several fr4 plate gerbers for various cutiepie/orthopie layouts.
2023-12-03 Updated fabrication files for dual-stagger and ortho PCBs and plates. Added stabilizer support for dual-stagger ISO P-key. Updated readme. Updated part mumbers in BOMs and corrected position files. A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
2023-12-11 add symmetrical ortho case top with middle blocker
2024-01-21 added thick plate models
2024-01-21 updated read me
